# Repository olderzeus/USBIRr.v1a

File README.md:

USB/Serial Infrared receiver based on the work of Ian from Hack-A-Day. 

http://hackaday.com/2008/10/30/how-to-usb-remote-control-receiver/

PCB Designs and Schematics

hackaday.com-ir-receiver-v1a 			-		Original design from Hack-A-Day
hackaday.com-ir-receiver-v1.4a			-		Modified design using a TSOP4838 and Surface mount PIC 18F2455

Aims and goals for this project. 

Implement RC6 protocol decoder
Allow user configurable protocols
Implement the serial IO port
Allow configuration to be stored in the EEPROM
Optimise the PCB designs to minimise the use of vias and create a fully surface mount ultra miniature version.

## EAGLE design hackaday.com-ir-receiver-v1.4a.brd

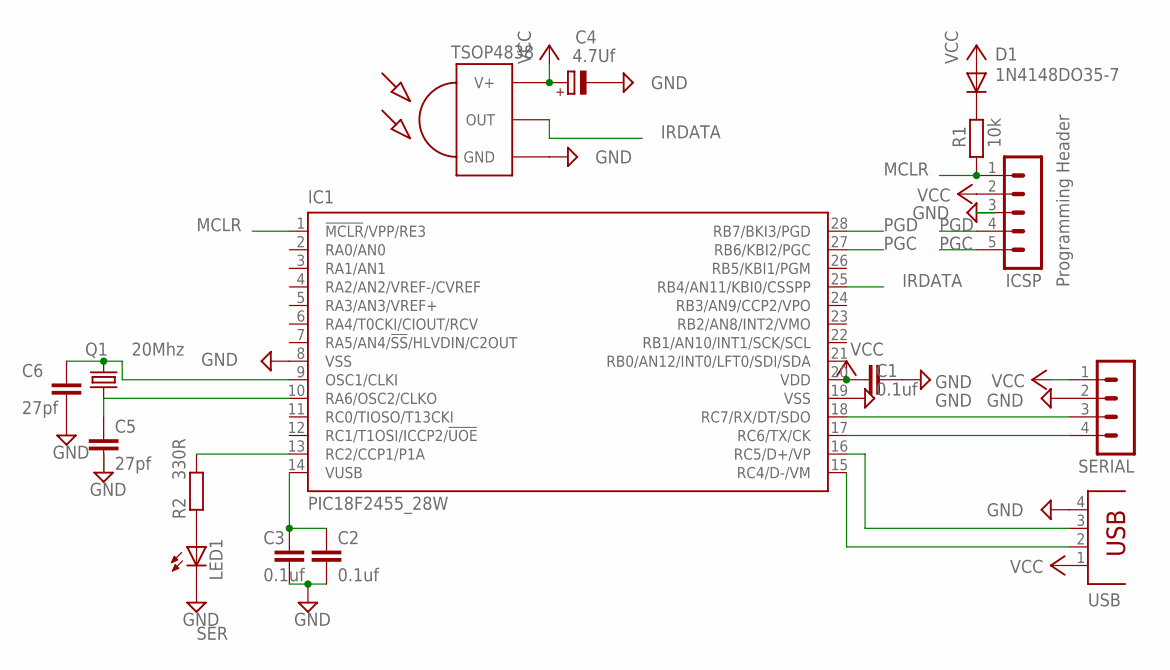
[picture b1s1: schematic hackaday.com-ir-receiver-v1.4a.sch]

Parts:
C1, C2, C3: 0.1uf; C025-024X044
C4: 4.7Uf; E2,5-5
C5, C6: 27pf; C025-024X044
D1: 1N4148DO35-7; DO35-7
IC1: PIC18F2455_28W; SO28W; MPN PIC18F2455-I/SO
ICSP: MA05-1
LED1: LED3MM
Q1: 20Mhz; HC49U-V
R1: 10k; 0204V
R2: 330R; 0204V
SERIAL: MA04-1
TSOP-1738: TSOP4838; TSOP18XX
USB: PN61729

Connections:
CLKI: C6.1, IC1.9 (OSC1/CLKI), Q1.2
CLKO: C5.1, IC1.10 (RA6/OSC2/CLKO), Q1.1
GND: C1.2, C2.2, C3.2, C4.-, C5.2, C6.2, IC1.8 (VSS), IC1.19 (VSS), ICSP.3, LED1.K (C), SERIAL.2, TSOP-1738.GND, USB.4
IRDATA: IC1.25 (RB4/AN11/KBI0/CSSPP), TSOP-1738.OUT
MCLR: IC1.1 (!MCLR!/VPP/RE3), ICSP.1, R1.1
unnamed: C2.1, C3.1, IC1.14 (VUSB)
unnamed: IC1.17 (RC6/TX/CK), SERIAL.4
unnamed: IC1.18 (RC7/RX/DT/SDO), SERIAL.3
unnamed: LED1.A, R2.1
unnamed: D1.C, R1.2
unnamed: IC1.13 (RC2/CCP1/P1A), R2.2
PGC: IC1.27 (RB6/KBI2/PGC), ICSP.5
PGD: IC1.28 (RB7/BKI3/PGD), ICSP.4
RC4: IC1.15 (RC4/D-/VM), USB.2
RC5: IC1.16 (RC5/D+/VP), USB.3
VCC: C1.1, C4.+, D1.A, IC1.20 (VDD), ICSP.2, SERIAL.1, TSOP-1738.VCC (V+), USB.1

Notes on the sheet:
SER
Programming Header

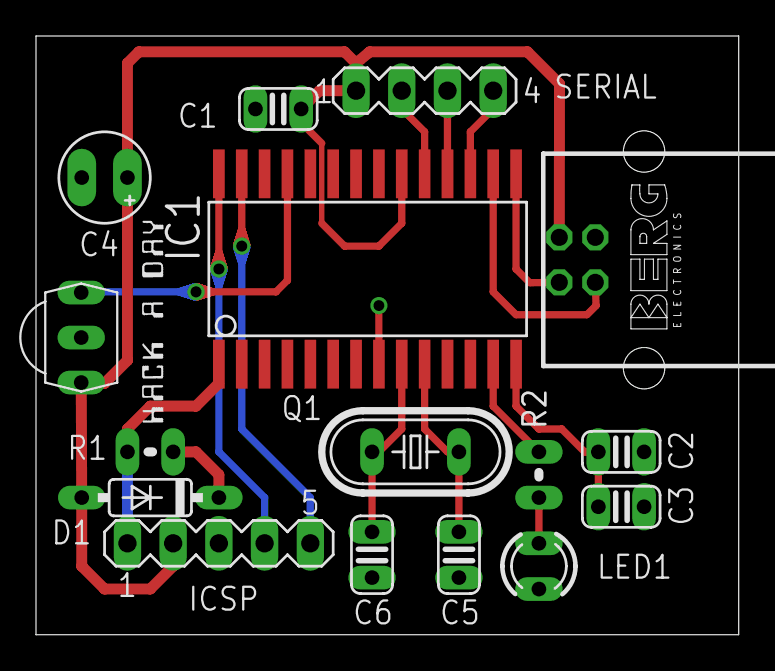
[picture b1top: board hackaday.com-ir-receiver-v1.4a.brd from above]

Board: 2 copper layers, 39.0 x 33.3 mm, 17 parts (0 on the bottom side), 16 nets.

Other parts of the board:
U$1: HACKADAY-TEXT-ONLY

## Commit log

2012-11-11 Changed directory structure.
    Added Readme file,
    Updated direcory structure
    Added images of the v1a and v1.4a designs
2012-11-11 Updated gitnore
    Added exception for library backup files.
